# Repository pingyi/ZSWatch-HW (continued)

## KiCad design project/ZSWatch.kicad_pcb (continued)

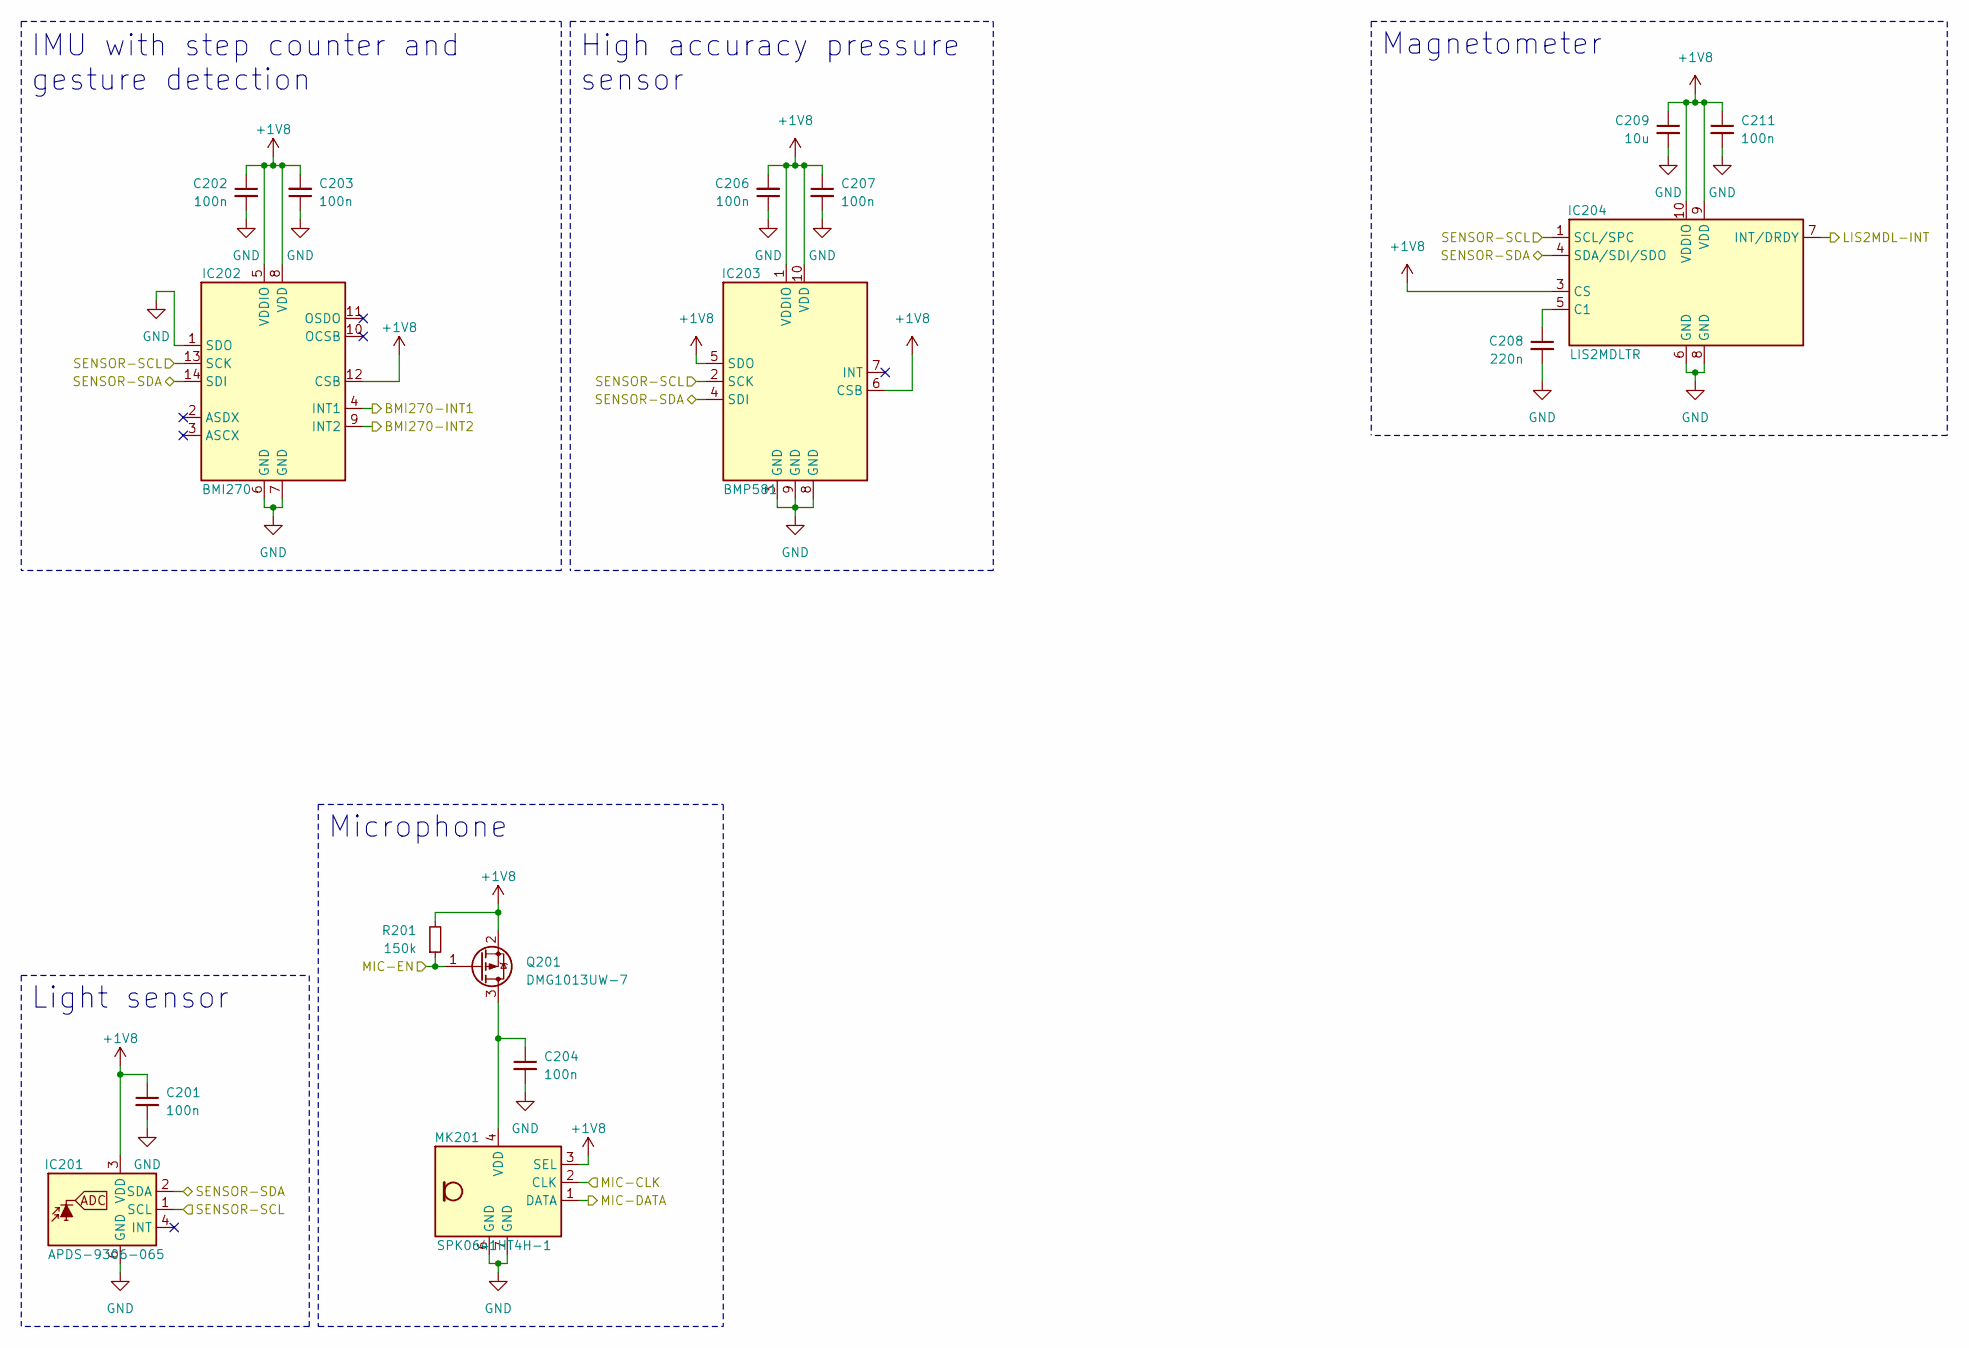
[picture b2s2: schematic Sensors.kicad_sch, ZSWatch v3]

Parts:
C201, C202, C203, C204, C206, C207, C211: 100n; C_0603_1608Metric
C208: 220n; C_0603_1608Metric
C209: 10u; C_0603_1608Metric
IC201: APDS-9306-065; Broadcom_DFN-6_2x2mm_P0.65mm
IC202: BMI270; Bosch_LGA-14_3x2.5mm_P0.5mm_LayoutBorder3x4y
IC203: BMP581; Bosch_LGA-10_2x2mm_P0.5mm_ClockwisePinNumbering
IC204: LIS2MDLTR; LGA-12_2x2mm_P0.5mm
MK201: SPK0641HT4H-1
Q201: DMG1013UW-7; SOT-323_SC-70
R201: 150k; R_0603_1608Metric

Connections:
+1V8: C201.1, C202.1, C203.2, C206.2, C207.1, C209.1, C211.1, IC201.3 (VDD), IC202.5 (VDDIO), IC202.8 (VDD), IC202.12 (CSB), IC203.1 (VDDIO), IC203.5 (SDO), IC203.6 (CSB), IC203.10 (VDD), IC204.3 (CS), IC204.9 (VDD), IC204.10 (VDDIO), MK201.3 (SEL), Q201.2 (S), R201.2; also elsewhere on the board
/MCU/BMI270-INT1: IC202.4 (INT1); also elsewhere on the board
/MCU/BMI270-INT2: IC202.9 (INT2); also elsewhere on the board
/MCU/LIS2MDL-INT: IC204.7 (INT/DRDY); also elsewhere on the board
/MCU/MIC-CLK: MK201.2 (CLK); also elsewhere on the board
/MCU/MIC-DATA: MK201.1 (DATA); also elsewhere on the board
/MCU/MIC-EN: Q201.1 (G), R201.1; also elsewhere on the board
/MCU/SENSOR-SCL: IC201.1 (SCL), IC202.13 (SCK), IC203.2 (SCK), IC204.1 (SCL/SPC); also elsewhere on the board
/MCU/SENSOR-SDA: IC201.2 (SDA), IC202.14 (SDI), IC203.4 (SDI), IC204.4 (SDA/SDI/SDO); also elsewhere on the board
GND: C201.2, C202.2, C203.1, C204.2, C206.1, C207.2, C208.2, C209.2, C211.2, IC201.6 (GND), IC202.1 (SDO), IC202.6 (GND), IC202.7 (GND), IC203.3 (GND), IC203.8 (GND), IC203.9 (GND), IC204.6 (GND), IC204.8 (GND), MK201.5 (GND), MK201.6 (GND), MK201.7 (GND), MK201.8 (GND); also elsewhere on the board
unnamed: C208.1, IC204.5 (C1)
unnamed: C204.1, MK201.4 (VDD), Q201.3 (D)

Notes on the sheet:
Magnetometer
High accuracy pressure sensor
Microphone
Light sensor
IMU with step counter and gesture detection

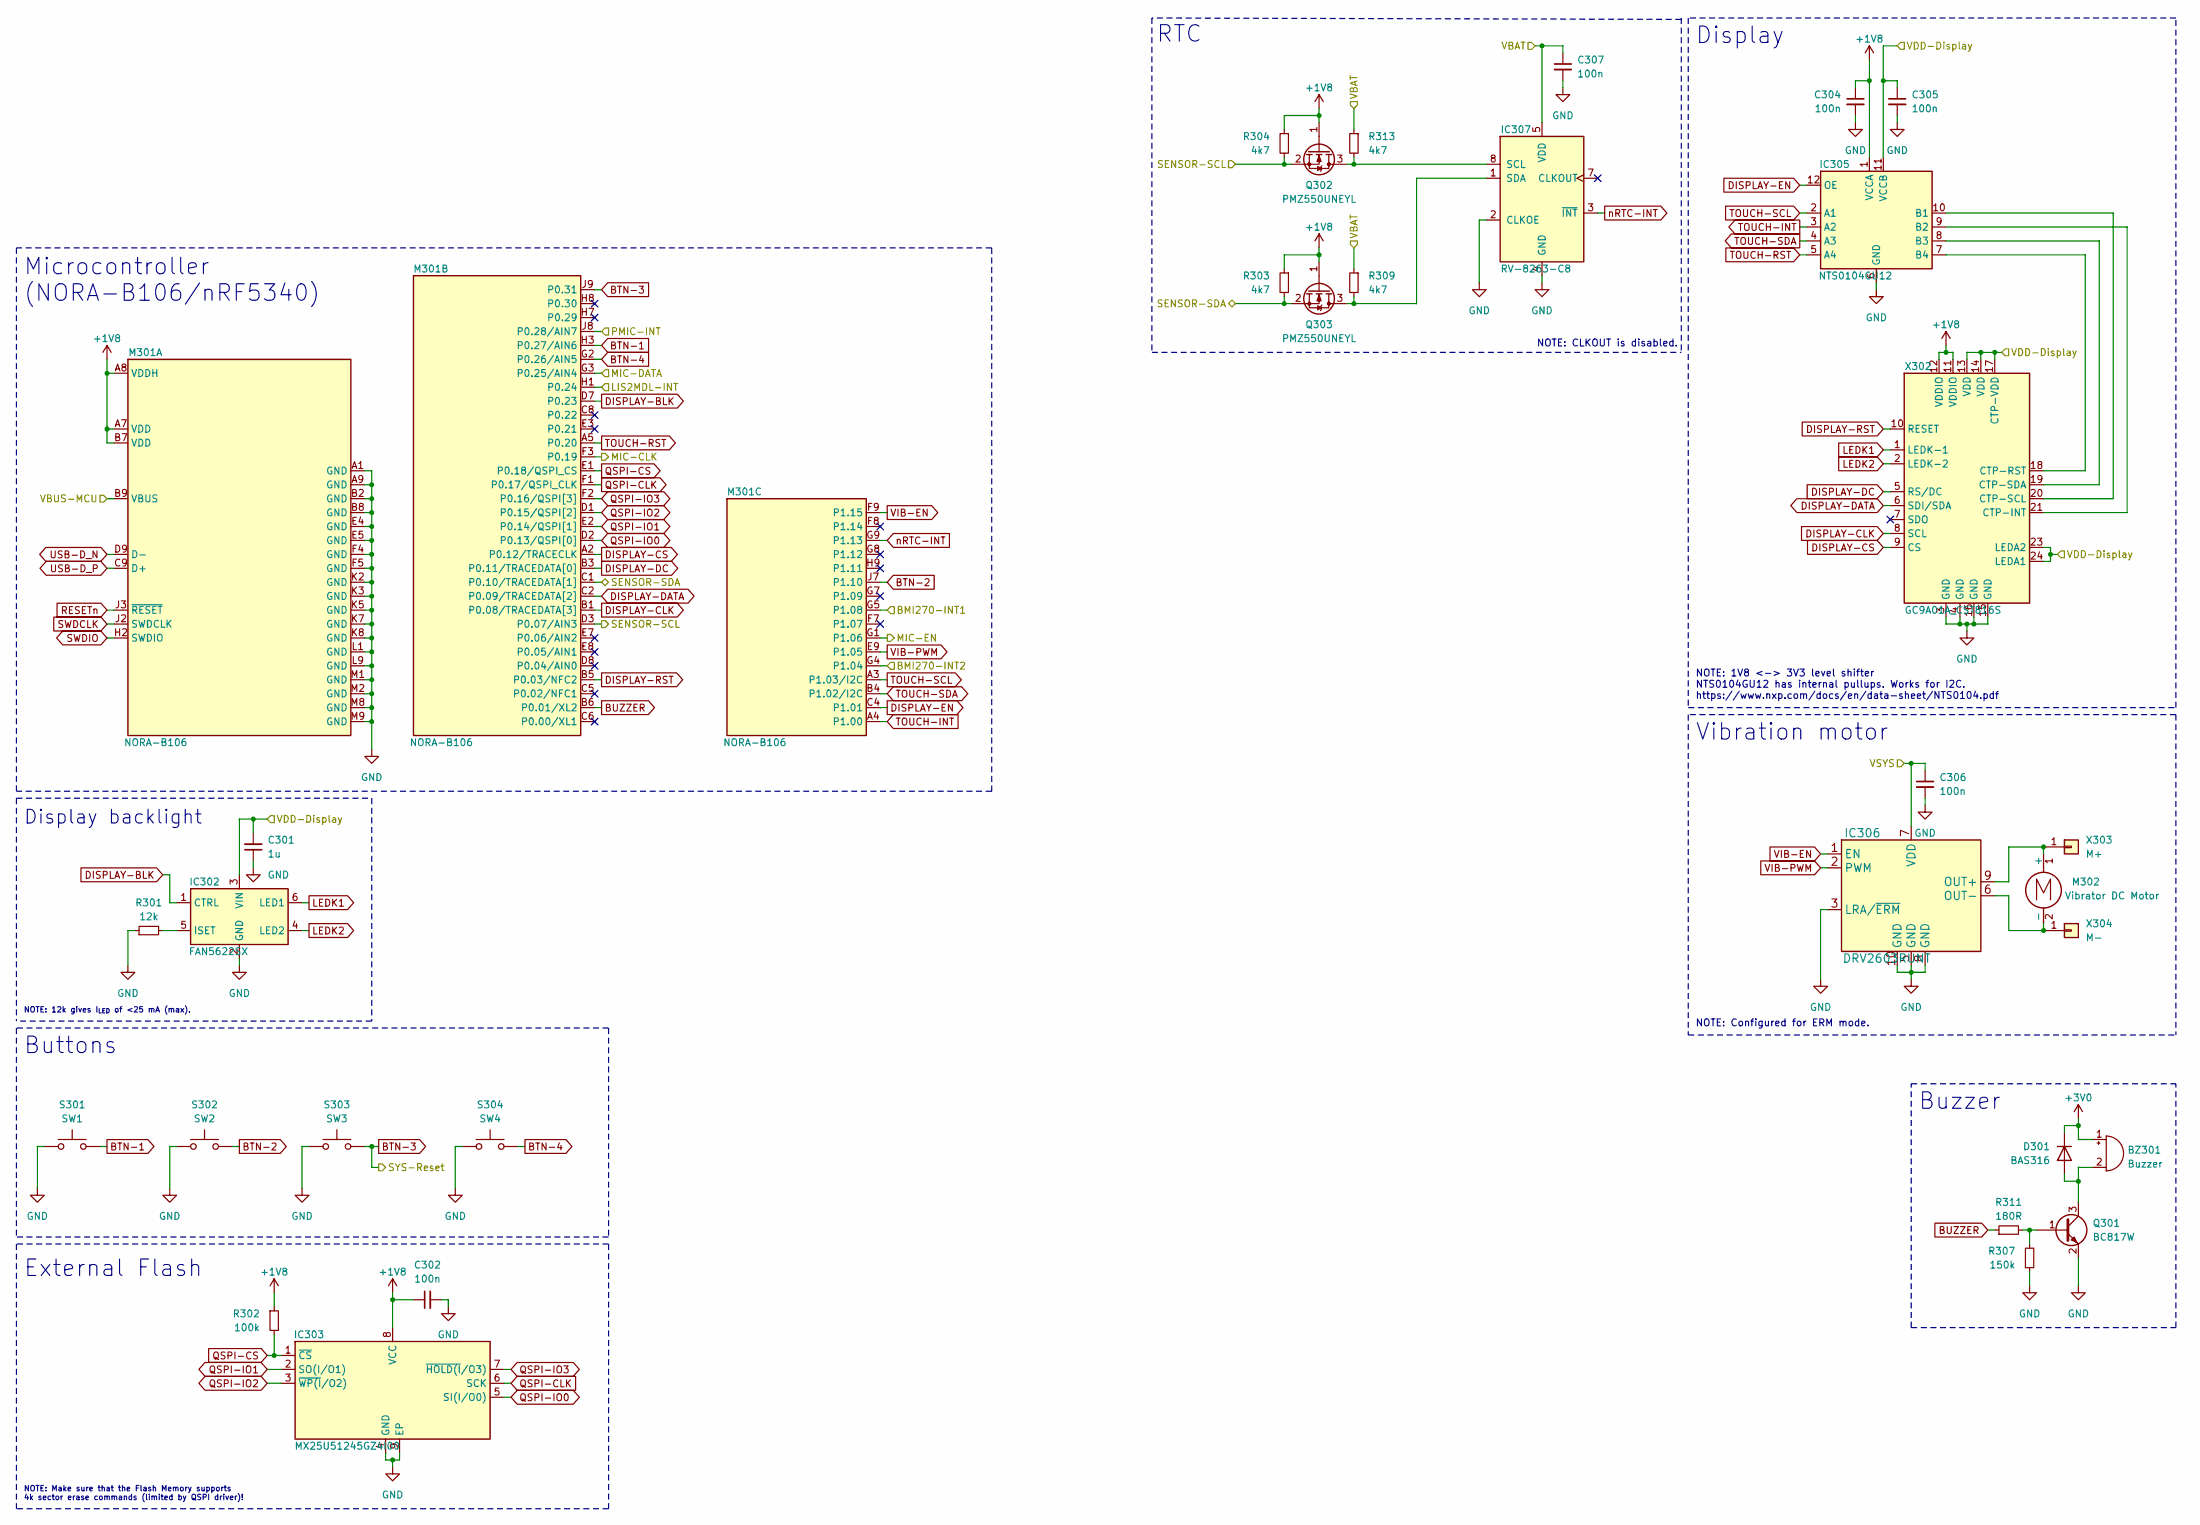
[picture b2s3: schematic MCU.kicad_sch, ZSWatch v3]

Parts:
BZ301: Buzzer; CMT-322-65-SMT-TR
C301: 1u; C_0603_1608Metric
C302, C304, C305, C306: 100n; C_0603_1608Metric
C307: 100n; C_0402_1005Metric
D301: BAS316; D_SOD-323
IC302: FAN5622SX; TSOT-23-6
IC303: MX25U51245GZ4I00; WSON-8-1EP_8x6mm_P1.27mm_EP3.4x4.3mm
IC305: NTS0104GU12; XQFN-12-1.7x2mm_P0.4mm
IC306: DRV2603RUNT; WQFN-10_2x2mm_P0.5mm
IC307: RV-8263-C8
M301: NORA-B106
M302: Vibrator DC Motor
Q301: BC817W; SOT-323_SC-70
Q302, Q303: PMZ550UNEYL; SOT-883
R301: 12k; R_0603_1608Metric
R302: 100k; R_0603_1608Metric
R303, R304: 4k7; R_0603_1608Metric
R307: 150k; R_0603_1608Metric
R309, R313: 4k7; R_0402_1005Metric
R311: 180R; R_0603_1608Metric
S301: SW1; TL6340AF160Q_Modified
S302: SW2; TL6340AF160Q_Modified
S303: SW3; TL6340AF160Q_Modified
S304: SW4; TL6340AF160Q_Modified
X302: GC9A01A_CST816S; ER-CON0.4-24P
X303: M+; TestPoint_Pad_1.0x1.0mm
X304: M-; TestPoint_Pad_1.0x1.0mm

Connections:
+1V8: C302.1, C304.1, IC303.8 (VCC), IC305.1 (VCCA), M301.A7 (VDD), M301.A8 (VDDH), M301.B7 (VDD), Q302.1 (G), Q303.1 (G), R302.1, R303.1, R304.1, X302.11 (VDDIO), X302.12 (VDDIO); also elsewhere on the board
+3V0: BZ301.1 (+), D301.1 (K); also elsewhere on the board
/MCU/BMI270-INT1: M301.G5 (P1.08); also elsewhere on the board
/MCU/BMI270-INT2: M301.G4 (P1.04); also elsewhere on the board
/MCU/LIS2MDL-INT: M301.H1 (P0.24); also elsewhere on the board
/MCU/MIC-CLK: M301.F3 (P0.19); also elsewhere on the board
/MCU/MIC-DATA: M301.G3 (P0.25/AIN4); also elsewhere on the board
/MCU/MIC-EN: M301.G1 (P1.06); also elsewhere on the board
/MCU/PMIC-INT: M301.J8 (P0.28/AIN7); also elsewhere on the board
/MCU/SENSOR-SCL: M301.D3 (P0.07/AIN3), Q302.2 (S), R304.2; also elsewhere on the board
/MCU/SENSOR-SDA: M301.C1 (P0.10/TRACEDATA[1]), Q303.2 (S), R303.2; also elsewhere on the board
/MCU/VBAT: C307.1, IC307.5 (VDD), R309.1, R313.1; also elsewhere on the board
/MCU/VBUS-MCU: M301.B9 (VBUS); also elsewhere on the board
/MCU/VDD-Display: C301.2, C305.1, IC302.3 (VIN), IC305.11 (VCCB), X302.13 (VDD), X302.14 (VDD), X302.17 (CTP-VDD), X302.23 (LEDA2), X302.24 (LEDA1); also elsewhere on the board
/MCU/VSYS: C306.1, IC306.7 (VDD); also elsewhere on the board
BTN-1: M301.H3 (P0.27/AIN6), S301.1
BTN-2: M301.J7 (P1.10), S302.2
BTN-3: M301.J9 (P0.31), S303.2; also elsewhere on the board
BTN-4: M301.G2 (P0.26/AIN5), S304.1
BUZZER: M301.B6 (P0.01/XL2), R311.1
DISPLAY-BLK: IC302.1 (CTRL), M301.D7 (P0.23)
DISPLAY-CLK: M301.B1 (P0.08/TRACEDATA[3]), X302.8 (SCL)
DISPLAY-CS: M301.A2 (P0.12/TRACECLK), X302.9 (CS)
DISPLAY-DATA: M301.C2 (P0.09/TRACEDATA[2]), X302.6 (SDI/SDA)
DISPLAY-DC: M301.B3 (P0.11/TRACEDATA[0]), X302.5 (RS/DC)
DISPLAY-EN: IC305.12 (OE), M301.C4 (P1.01)
DISPLAY-RST: M301.B5 (P0.03/NFC2), X302.10 (RESET)
GND: C301.1, C302.2, C304.2, C305.2, C306.2, C307.2, IC302.2 (GND), IC303.4 (GND), IC303.9 (EP), IC305.6 (GND), IC306.3 (LRA/~ERM), IC306.5 (GND), IC306.8 (GND), IC306.10 (GND), IC307.2 (CLKOE), IC307.4 (GND), M301.A1 (GND), M301.A9 (GND), M301.B2 (GND), M301.B8 (GND), M301.E4 (GND), M301.E5 (GND), M301.F4 (GND), M301.F5 (GND), M301.K2 (GND), M301.K3 (GND), M301.K5 (GND), M301.K7 (GND), M301.K8 (GND), M301.L1 (GND), M301.L9 (GND), M301.M1 (GND), M301.M2 (GND), M301.M8 (GND), M301.M9 (GND), Q301.2 (E), R301.1, R307.1, S301.2, S302.1, S303.1, S304.2, X302.3 (GND), X302.4 (GND), X302.15 (GND), X302.16 (GND); also elsewhere on the board
LEDK1: IC302.6 (LED1), X302.1 (LEDK-1)
LEDK2: IC302.4 (LED2), X302.2 (LEDK-2)
unnamed: BZ301.2 (-), D301.2 (A), Q301.3 (C)
unnamed: IC302.5 (ISET), R301.2
unnamed: IC305.10 (B1), X302.20 (CTP-SCL)
unnamed: IC305.9 (B2), X302.21 (CTP-INT)
unnamed: IC305.8 (B3), X302.19 (CTP-SDA)
unnamed: IC305.7 (B4), X302.18 (CTP-RST)
unnamed: IC306.9 (OUT+), M302.1 (+), X303.1
unnamed: IC306.6 (OUT-), M302.2 (-), X304.1
unnamed: IC307.8 (SCL), Q302.3 (D), R313.2
unnamed: IC307.1 (SDA), Q303.3 (D), R309.2
unnamed: Q301.1 (B), R307.2, R311.2
QSPI-CLK: IC303.6 (SCK), M301.F1 (P0.17/QSPI_CLK)
QSPI-CS: IC303.1 (~CS), M301.E1 (P0.18/QSPI_CS), R302.2
QSPI-IO0: IC303.5 (SI(I/O0)), M301.D2 (P0.13/QSPI[0])
QSPI-IO1: IC303.2 (SO(I/O1)), M301.E2 (P0.14/QSPI[1])
QSPI-IO2: IC303.3 (~WP(I/O2)), M301.D1 (P0.15/QSPI[2])
QSPI-IO3: IC303.7 (~HOLD(I/O3)), M301.F2 (P0.16/QSPI[3])
RESETn: M301.J3 (~RESET)
SWDCLK: M301.J2 (SWDCLK)
SWDIO: M301.H2 (SWDIO)
TOUCH-INT: IC305.3 (A2), M301.A4 (P1.00)
TOUCH-RST: IC305.5 (A4), M301.A5 (P0.20)
TOUCH-SCL: IC305.2 (A1), M301.A3 (P1.03/I2C)
TOUCH-SDA: IC305.4 (A3), M301.B4 (P1.02/I2C)
USB-D_N: M301.D9 (D-)
USB-D_P: M301.C9 (D+)
VIB-EN: IC306.1 (EN), M301.F9 (P1.15)
VIB-PWM: IC306.2 (PWM), M301.E9 (P1.05)
nRTC-INT: IC307.3 (~INT), M301.G9 (P1.13)

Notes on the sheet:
NOTE: CLKOUT is disabled.
Buttons
NOTE: 12k gives I_{LED} of <25 mA (max).
Vibration motor
Buzzer
NOTE: Make sure that the Flash Memory supports 4k sector erase commands (limited by QSPI driver)!
RTC
Display
NOTE: 1V8 <-> 3V3 level shifter NTS0104GU12 has internal pullups. Works for I2C. https://www.nxp.com/docs/en/data-sheet/NTS0104.pdf
Microcontroller (NORA-B106/nRF5340)
Display backlight
NOTE: Configured for ERM mode.
External Flash

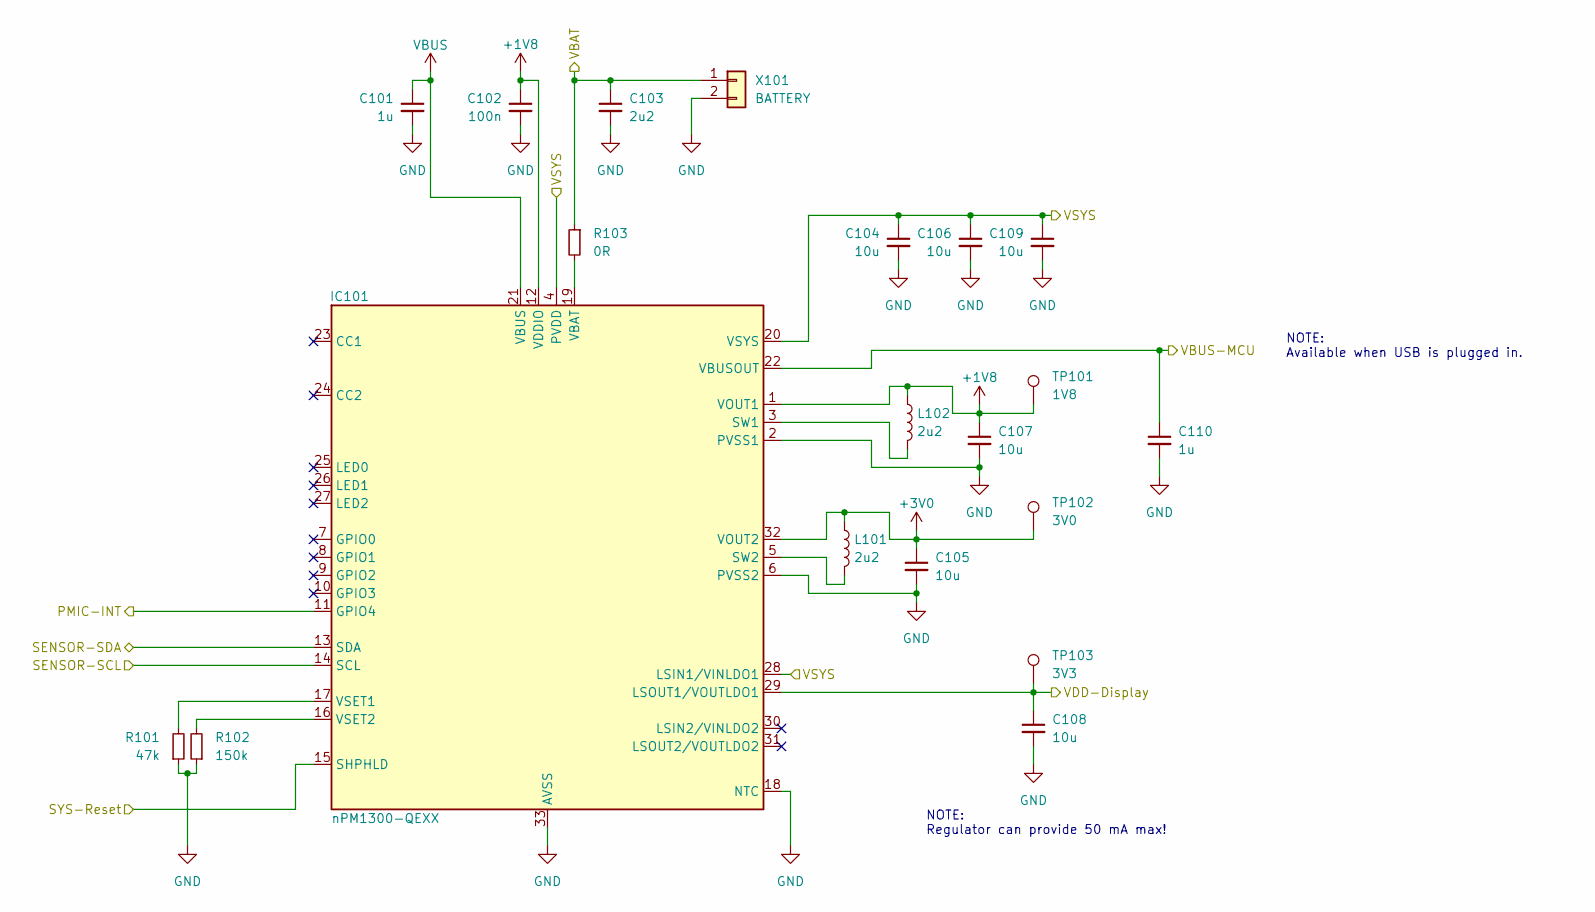
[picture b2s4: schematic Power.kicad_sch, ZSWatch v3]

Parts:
C101, C110: 1u; C_0603_1608Metric
C102: 100n; C_0603_1608Metric
C103: 2u2; C_0603_1608Metric
C104, C105, C106, C107, C108, C109: 10u; C_0603_1608Metric
IC101: nPM1300-QEXX; QFN-32-1EP_5x5mm_P0.5mm_EP3.6x3.6mm_ThermalVias
L101, L102: 2u2; L_0806_2016
R101: 47k; R_0603_1608Metric
R102: 150k; R_0603_1608Metric
R103: 0R; R_0402_1005Metric
TP101: 1V8; TestPoint_Pad_D1.0mm
TP102: 3V0; TestPoint_Pad_D1.0mm
TP103: 3V3; TestPoint_Pad_D1.0mm
X101: BATTERY; 78171-0002

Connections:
+1V8: C102.1, C107.1, IC101.1 (VOUT1), IC101.12 (VDDIO), L102.1, TP101.1; also elsewhere on the board
+3V0: C105.1, IC101.32 (VOUT2), L101.1, TP102.1; also elsewhere on the board
/MCU/PMIC-INT: IC101.11 (GPIO4); also elsewhere on the board
/MCU/SENSOR-SCL: IC101.14 (SCL); also elsewhere on the board
/MCU/SENSOR-SDA: IC101.13 (SDA); also elsewhere on the board
/MCU/VBAT: C103.1, R103.1, X101.1; also elsewhere on the board
/MCU/VBUS-MCU: C110.1, IC101.22 (VBUSOUT); also elsewhere on the board
/MCU/VDD-Display: C108.1, IC101.29 (LSOUT1/VOUTLDO1), TP103.1; also elsewhere on the board
/MCU/VSYS: C104.1, C106.1, C109.1, IC101.4 (PVDD), IC101.20 (VSYS), IC101.28 (LSIN1/VINLDO1); also elsewhere on the board
BTN-3: IC101.15 (SHPHLD); also elsewhere on the board
GND: C101.2, C102.2, C103.2, C104.2, C105.2, C106.2, C107.2, C108.2, C109.2, C110.2, IC101.2 (PVSS1), IC101.6 (PVSS2), IC101.18 (NTC), IC101.33 (AVSS), R101.1, R102.1, X101.2; also elsewhere on the board
unnamed: IC101.3 (SW1), L102.2
unnamed: IC101.5 (SW2), L101.2
unnamed: IC101.19 (VBAT), R103.2
unnamed: IC101.17 (VSET1), R101.2
unnamed: IC101.16 (VSET2), R102.2
VBUS: C101.1, IC101.21 (VBUS)

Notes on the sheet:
NOTE: Available when USB is plugged in.
NOTE: Regulator can provide 50 mA max!

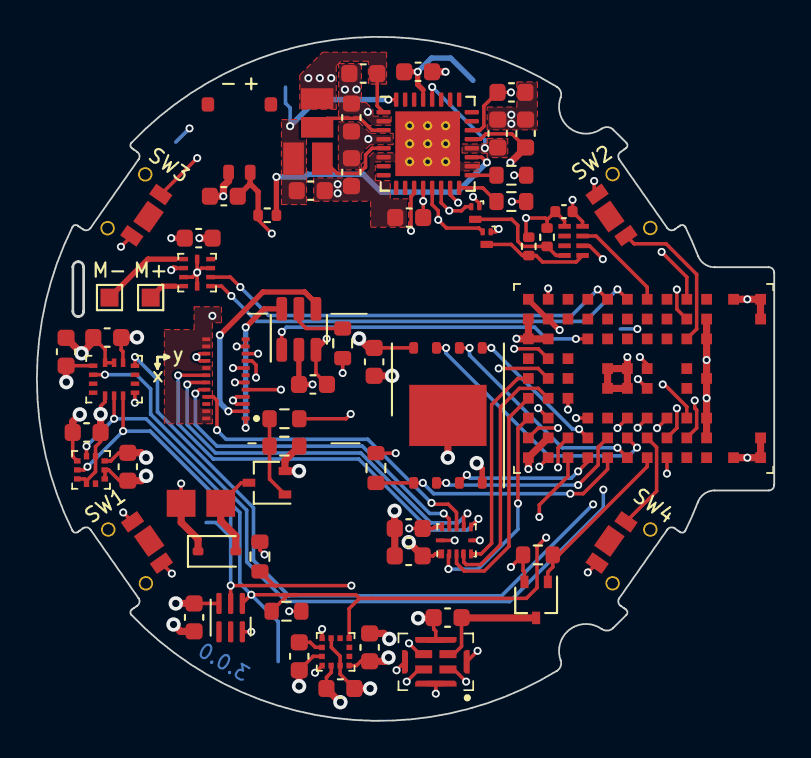
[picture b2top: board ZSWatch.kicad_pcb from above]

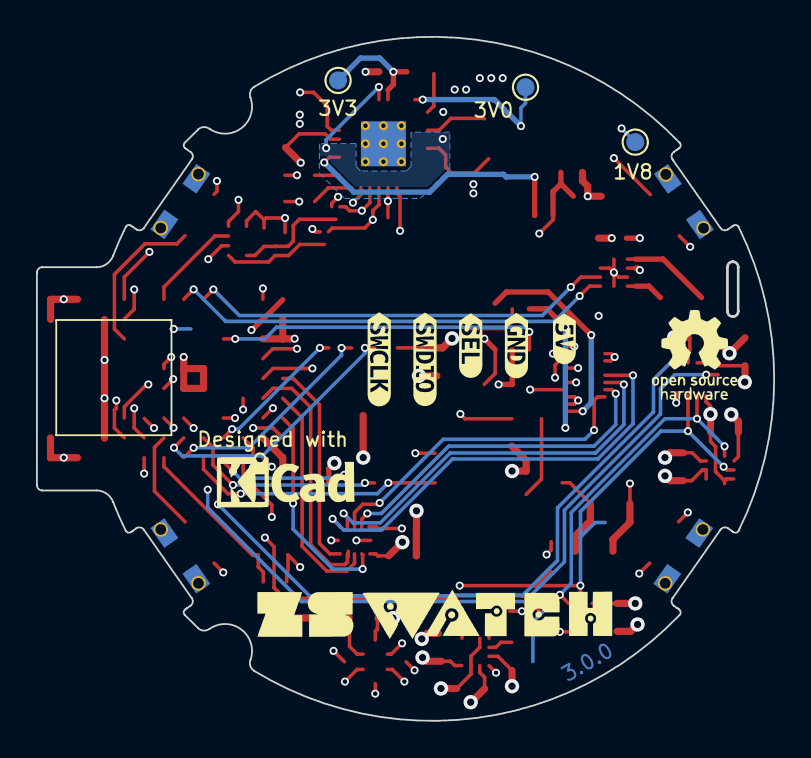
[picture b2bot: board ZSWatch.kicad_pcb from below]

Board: 4 copper layers, 41.0 x 38.0 mm, 73 parts (8 on the bottom side), 62 nets.

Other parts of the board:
kibuzzard-6616D313: G***; kibuzzard-6616D313
kibuzzard-656642B5: G***; kibuzzard-656642B5
kibuzzard-656642E4: G***; kibuzzard-656642E4
kibuzzard-65664337: G***; kibuzzard-65664337
kibuzzard-65664342: G***; kibuzzard-65664342

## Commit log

2025-04-06 Fix ci issue.
2025-05-08 PCB: Remove BME688 and USB switch
    - Implement #106
    - Remove USB switch and the required components
2025-05-08 Project: Port to KiCad 9
    - Port to KiCad 9.0.1
    Closes #101
2025-05-08 KiBot: Enhance KiBot configuration
    - Implement #110
    - Implement #109
    - Add refresh for PCB specifications
    - Add refresh for stackup
2025-05-09 PCB: Add new vibration motor
    - Remove old hardware project (comes back later)
    - Add new dev-kit project
    Closes #102
2025-05-09 Add 0805 resistors for current measurement, reorganize schematics
2025-05-18 Working on the layout for the dev kit
2025-05-20 Add more documentation
2025-05-20 Add CI/CD pipeline for Dev-Kit, more Dev-Kit improvements
2025-05-20 Add image from CI/CD action
2025-05-23 git commit -m "PCB: Tweak silkscreen and headers.
    - Added silkscreen labels to headers.
    - Added function text to buttons.
    - Made PCB 5mm wider (left) to make space for display (not sticking out of PCB) and allow more centered
    buttons placement.
    - Add header for UART pins (good in case we don't have a working dock built) (no mount).
    - Changed from TP to header for VBAT for alternative way to connect battery (no mount).
2025-05-23 PCB: Tweak silkscreen and headers.
    - Added silkscreen labels to headers.
    - Added function text to buttons.
    - Made PCB 5mm wider (left) to make space for display (not sticking out of PCB) and allow more centered
    buttons placement.
    - Add header for UART pins (good in case we don't have a working dock built) (no mount).
    - Changed from TP to header for VBAT for alternative way to connect battery (no mount).
2025-05-23 Fix wrong display SPI lines
2025-05-23 Disable diff workflow for pushes and set it to manually
2025-05-23 Add mounting holes for the display
2025-05-23 Changes from Jacob
2025-05-24 Add impedance matching for USB, add jumper caps
2025-05-25 Cosmetic changes
2025-05-25 Add fabrication layer to KiBot iBom
2025-05-28 Copy ref documents and images into 'other' directory for ordering
2025-05-28 Fix wrong part number for R102 and R201
2025-05-29 Fix wrong BOM generation for Kibot
2025-05-29 Temporary remove zipping of other directory
2025-05-29 Fix wrong BOM generation
2025-05-29 Change top and bottom copper to 1oz
2025-05-29 Fix wrong part number
2025-05-29 Bring back prints
2025-05-30 Fix wrong part numbers
2025-09-06 Release Watch-DK revision 1
    - Remove PCB prints from directory
2025-09-06 Bug: Issue #117
2025-09-06 Feature: Issue #149
2025-09-06 Fix CI/CD issues
2025-09-06 Task: Issue #124
2025-09-06 Task: Issue #122
2025-09-06 Task: Issue #135
2025-09-06 Task: Issue #115
2025-09-06 Bug: Issue #121
2025-09-06 Increase length of QSPI Clock line to avoid timing issues
2025-09-06 Feature: Issue #145
    - Update symbols
2025-09-06 doc: CI/CD fixes, documentation updates
    - Fix wrong part number for SWD connector
    - Fix missing footprint for RTC level shifter
2025-09-06 Bug: Issue #146
2025-09-06 Bug: Issue #132
2025-09-06 Bug: Issue #134
2025-09-06 Feature: Issue #153
2025-09-06 Silkscreen tweaking and formatting.
    - Remove ZSWatch logo and url as it is part of UV print
    - Add silkscreen to HR header
2025-09-06 Task: Issue #129
2025-09-06 Add jobset for generating all svg files for UV printing.
2025-09-06 Feature: Issue #128
2025-09-06 Feature: Issue #116
2025-09-06 Bug: Issue #127
2025-09-06 Task: Issue #154
2025-09-06 doc: Add missing drill table, update impedance table
2025-09-06 Feature: Issue #131
    - Fix wrong page numbers
    - Update reference designators to match the page numbers
2025-09-06 Feature: Issue #133
2025-09-06 Task: Issue #130
2025-09-06 Task: Issue #125
2025-09-06 Task: Issue #123
2025-09-17 Release 1.2.0
    - Remove old files
    - Update CI/CD pipeline
    - Fix ERC issues
    - Fix DRC issues
    - Update README
    - Add changelog for v1.2.0
2025-09-17 Add 'Resources' section to README
2025-09-17 Update CHANGELOG
2025-09-19 Push outputs from CI/CD (2025-09-19 07:31:13)
